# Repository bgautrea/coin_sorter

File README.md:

# Coin Sorter — Computer Vision Pipeline

Real-time coin classifier for an automated sorter. Camera on a Raspberry Pi 5
watches a belt, an ONNX classifier identifies each coin (penny / nickel / dime
/ quarter / reject), and a serial command tells a Raspberry Pi Pico to route
the coin to the correct bin.

```
   CSI camera ──► Pi 5 ──► picamera2 ──► OpenCV ──► ONNX Runtime ──► label, conf
                                                                       │
                                                  USB serial @ 115200 ─┴──► Pico ──► diverter
```

Training happens off-Pi (Google Colab, T4). The Pi never installs torch or
ultralytics — only `onnxruntime` for inference.

## Repo layout

```
coin_sorter/
├── pyproject.toml
├── config.yaml
├── src/coin_sorter/
│   ├── __init__.py    # load_config, configure_logging
│   ├── capture.py     # CLI: capture labelled frames on the Pi
│   ├── dataset.py     # PyTorch Dataset used by the Colab notebook
│   ├── train.py       # reference CLI mirror of the notebook
│   ├── infer.py       # CoinClassifier — ONNX Runtime, with stub fallback
│   ├── pico.py        # serial wrapper for the Pico belt controller
│   └── sorter.py      # main runtime loop
├── notebooks/train_colab.ipynb
├── scripts/zip_dataset.sh, fetch_model.sh
├── data/raw/, data/processed/   (gitignored)
├── models/                       (gitignored)
└── tests/
```

## Pi-side setup (Raspberry Pi OS Bookworm)

### 1. System packages

```bash
sudo apt update
sudo apt install -y \
    python3-picamera2 \
    python3-libcamera \
    python3-pip \
    python3-venv \
    libatlas-base-dev \
    git \
    zip
```

`python3-picamera2` brings in `libcamera` and the Pi-specific camera stack —
those bits are not available from PyPI on the Pi and must come from apt.

### 2. Virtual environment (with system site packages)

Bookworm enforces [PEP 668](https://peps.python.org/pep-0668/) — pip into the
system Python is blocked, and you should not use `--break-system-packages`.
Use a venv. **Critical:** `picamera2` has C extensions tied to the system
`libcamera` build, so the venv has to inherit system site-packages:

```bash
cd ~/coin_sorter
python3 -m venv --system-site-packages .venv
source .venv/bin/activate
pip install --upgrade pip
pip install -e .
```

Verify picamera2 is visible inside the venv:

```bash
python -c "from picamera2 import Picamera2; print('ok')"
```

If you forgot `--system-site-packages`, recreate the venv — installing
picamera2 from PyPI on the Pi is more pain than it is worth.

### 3. Confirm camera + Pico

```bash
libcamera-hello --list-cameras   # should show the Module 3
ls /dev/ttyACM*                  # should show /dev/ttyACM0
groups | tr ' ' '\n' | grep dialout || sudo usermod -aG dialout "$USER"
# log out / back in after adding to dialout
```

## Data capture workflow

Capture is **belt-fed**: a feeder stepper drops coins onto the belt, they pass
under the camera, and a **single-coin gate** decides what gets saved. Each save
is a tight square crop around one whole, isolated coin.

### Labels: (denomination, design, side)

The goal is to pull collectible varieties out of a mixed batch, and the
identifying design is often on **one side only** (a wheat cent's obverse is the
same Lincoln as a memorial cent). So classes are `denomination_design_side`,
e.g. `penny_wheat_rev`, `nickel_buffalo_obv` — see `classifier.labels` in
`config.yaml`, and `sorter.sort_map` for which labels go to the `keep` /
`common` / `check` bins. The `check` bin (coins ambiguous from the visible
side) is simply re-fed: each pass halves it.

The capture flow that follows from this is: **feed one design per batch**, then
**tag sides in the web UI** afterwards (a coin lands heads-up or tails-up at
random).

### Lighting recipe (rig-specific, in `config.local.yaml`)

The internal ring light mirrors off the belt as a specular streak that breaks
detection; the working recipe is the ring **off**, an off-axis **external
light** (switched by hand — check the preview is not black before a run), a
manual short shutter (`exposure_us: 1500`) to freeze belt motion, and manual
white balance. **Do not change WB between batches**: colour is the strongest
cue between denominations, and a WB drift inside one class teaches the model
the tint instead of the coin. Colour robustness comes from augmentation at
training time, applied uniformly to every class.

### Web UI

On the rig it runs as a user systemd service (`deploy/coin-webcal.service`):

```bash
scripts/webcal.sh install                 # once: install + enable at boot (sudo for linger)
scripts/webcal.sh start|stop|restart|status|logs   # shorthand for the commands below
systemctl --user restart coin-webcal      # after config.yaml / label changes
systemctl --user stop coin-webcal         # before CLI capture or flashing the Pico
journalctl --user-unit coin-webcal -f      # logs
python -m coin_sorter.webcal              # or run it by hand; http://<pi-ip>:8080/
```

Live preview with the detection overlay (`area`, `circ`, `fill`, and `sharp` —
a focus figure of merit; peak it on the *face* of a nickel sitting on the belt,
depth of field at this working distance is about ±1 mm), sliders for focus,
WB, exposure, ROI and gate thresholds, and the belt / feeder controls.

**Feeder**: speed plus *burst ms* / *every ms* pulsing. Pulsing is the
coin-spacing knob — the feeder runs in short bursts and the belt clears each
burst before the next. Working values for nickels: 3200 Hz, 300 ms every
1500 ms, belt 550 Hz. The firmware releases both stepper drivers 1 s after
motion stops (an idle TB6600 at full holding current cooked the feeder motor
once); check each driver's current DIPs against its motor's rating — the feeder
is a 0.7 A 17HS4023.

**Capture**: set the label to the *design* you loaded (e.g. `nickel_jefferson`
— the side is added when tagging), Start, then belt → feeder. The count climbs
only for crops that pass the gate.

**Tagging**: in the Captures panel enter the label, Refresh, then **Tag**. Each
crop is shown large; press the number key for its (design, side) class and it
is moved into that folder and the next one appears. `s` skips, `x` deletes,
`Esc` stops. Targets are the configured labels sharing the denomination prefix.

"Show config" emits a `config.local.yaml` snippet with the tuned camera values.
The web UI **owns the camera** — stop it before using the CLI below.

### The single-coin gate

Besides area and circularity, a blob must have `fill` (area ÷ its
min-enclosing-circle area; one coin ≈ 0.95, two overlapping ≈ 0.6) above
`min_fill_frac`, not touch the ROI border, and have no other blob inside its
crop window (`isolate`). Clusters and half-coins are never saved under a class
label. To re-gate crops captured earlier:

```bash
python scripts/prune_crops.py            # report per label
python scripts/prune_crops.py --apply    # move failures to data/raw/_rejected/<label>/
```

`_rejected/` is excluded from training and from `zip_dataset.sh`.

### CLI capture (alternative to the web UI)

```bash
python -m coin_sorter.capture --label _calib --calibrate      # ROI/threshold snapshot
python -m coin_sorter.capture --label nickel_jefferson --count 250 --drive-belt
python -m coin_sorter.capture --label reject --interval 0.4 --count 250   # bypasses the gate
```

`--count` counts coins saved. `dedup_mode` picks one save per coin
(`centroid_band`) or a few pose samples per coin (`min_interval`).

## Training workflow (Colab)

1. **Bundle the dataset on the Pi:**
   ```bash
   ./scripts/zip_dataset.sh
   ```
   Produces `./data.zip`.

2. **Upload to Drive** at `MyDrive/coin_sorter/data.zip`. The notebook reads
   this exact path.

3. **Open `notebooks/train_colab.ipynb` in Colab:**
   - Runtime → Change runtime type → T4 GPU
   - Runtime → Run all
   - The notebook mounts Drive, unzips, trains, prints top-1/top-5, writes a
     confusion matrix, exports ONNX, and copies the result to
     `MyDrive/coin_sorter/models/coin_classifier.onnx`.

4. **Pull the model back to the Pi:**
   ```bash
   # If you have Drive mounted on a workstation:
   ./scripts/fetch_model.sh user@workstation:/path/to/Drive/MyDrive/coin_sorter/models/coin_classifier.onnx

   # Or a local copy:
   ./scripts/fetch_model.sh ~/Downloads/coin_classifier.onnx
   ```
   The model lands at `models/coin_classifier.onnx` (the path in `config.yaml`).

## Deployment

```bash
source .venv/bin/activate
python -m coin_sorter.sorter
```

If `models/coin_classifier.onnx` is missing, the sorter logs a warning and
runs with a stub classifier that always returns `reject` with confidence 0.
This lets you verify the camera and Pico paths before any model exists.

## Configuration

Everything lives in `config.yaml`. Per-machine overrides go in
`config.local.yaml` (gitignored, deep-merged on top). The most useful knobs:

- `camera.width / height` — resolution. 1280×720 is plenty for the classifier
  and keeps frame rate up.
- `model.path` — where the ONNX model is loaded from.
- `model.input_size` — must match the `imgsz` you trained at.
- `classifier.confidence_threshold` — coins below this go to `reject`.
- `classifier.labels` — class order. **Must match alphabetical sort of the
  training class folders** (this is how Ultralytics assigns indices).
- `sorter.cooldown_ms` — guard against double-classifying the same coin.
- `camera.roi` — belt region as `[x, y, w, h]` fractions; capture crops to this.
- `camera.af_mode / lens_position` — Arducam 64MP focus (manual lock recommended
  for the fixed-distance belt; find the value in the web UI or cam_test/stream.py).
- `camera.awb / colour_gains` — white balance; lock it (manual `[red, blue]`) for
  consistent colour under the ring. Tune in the web UI (`coin_sorter.webcal`).
- `capture.*` — the belt-fed capture gate (segmentation method, area/circularity
  thresholds, dedup mode, crop padding). See "Data capture workflow" above and
  the inline comments in `config.yaml`.
- `capture.lights / light_rgb` — WS2812 ring light (Pico GP16); on for every
  session, neutral white by default.

## Troubleshooting

**`ModuleNotFoundError: picamera2`** — Your venv does not see system
site-packages. Recreate with `python -m venv --system-site-packages .venv`.

**`PermissionError: '/dev/ttyACM0'`** — You are not in the `dialout` group.
Run `sudo usermod -aG dialout $USER`, then log out and back in.

**`/dev/ttyACM0` missing** — The Pico is not enumerating. Check the USB cable
(many "charging" cables have no data lines), `dmesg | tail -20` for kernel
hints, or try a different USB port.

**`libcamera-hello` shows no cameras** — Confirm the CSI ribbon is seated
correctly, then ensure `dtoverlay=imx708` (Module 3) or the appropriate
overlay is enabled in `/boot/firmware/config.txt`. Reboot after changes.

**ONNX Runtime warns about provider** — The Pi build of `onnxruntime` from
PyPI ships with CPUExecutionProvider only. `XnnpackExecutionProvider` will
load only if you have an onnxruntime build with XNNPACK enabled; otherwise
CPU is fine — a YOLO-cls nano runs at >30 FPS at 224×224 on the Pi 5.

**Classifier always returns `reject` with confidence 0.0** — The stub is
active. Either the model file is missing, or the path in `config.yaml`
doesn't match where you placed it. Check `ls -lh models/`.

**Wrong class predicted consistently for one class** — Almost always a label-
order mismatch. The order of `classifier.labels` in `config.yaml` must match
`sorted(os.listdir(data_root))` from training time.

## Decisions worth flagging (see the Colab notebook for the full rationale)

- **Base model: YOLO11 nano-cls** by default. v11 trains a bit faster than v8
  for the same accuracy on small classification problems and the API is
  identical (`YOLO('yolo11n-cls.pt')`). Swap to `'yolov8n-cls.pt'` if you want
  to A/B; either is fine.
- **Image size: 224×224.** Coins-as-discs are low-frequency enough that this
  is plenty. If you later need to distinguish e.g. state quarter designs,
  bump to 320 or 384 (and update both `training.imgsz` and `model.input_size`).
- **Class imbalance.** Easiest fix is collecting balanced data — aim for the
  same image count per class. If that's impractical, oversample the minority
  classes (Ultralytics doesn't expose loss weighting cleanly for cls). The
  notebook prints a confusion matrix — watch for one row consistently mis-
  classified, that's the signal.
- **Augmentation.** Full 360° rotation is non-optional (coins land in any
  orientation). HSV jitter handles copper-vs-silver lighting drift. Avoid
  random crop / perspective — those distort the coin's circular outline,
  which is genuine signal.
- **ONNX export.** `dynamic=False` + fixed `imgsz` gives the smallest, fastest
  graph. Opset 17 is well-supported by onnxruntime 1.17+. If you ever change
  `imgsz`, re-export — input shape is baked in.

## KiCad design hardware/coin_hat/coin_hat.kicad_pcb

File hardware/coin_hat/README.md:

# Coin sorter HAT+ — rev 1

KiCad project for a Pi 5 HAT+ that carries the whole motion side of the
sorter: 12 V in, buck to 5 V for the Pi, a Raspberry Pi Pico, two StepStick
sockets (TMC2209 or A4988, selected by solder jumpers) for belt and feeder, the
MG996R diverter servo on its own buck, switched 12 V outputs, and the small
stuff (LED ring level shifter, feeder home switch, coin sensor, HAT+ ID EEPROM).

The board runs **lengthwise** along the Pi: 122 × 56.5 mm, the same width as the
Pi. The HAT+ holes and header sit at one end, and a 57 mm overhang runs past the
Pi's SD-card / PCIe end, so the drivers, jack and bucks sit over nothing. The
Pi + HAT stack is 142 × 56.5 mm, a slim box instead of rev 0's 85 × 90. The
overhang goes off the SD end, not the USB end: at 16 mm spacer height, a board
over the USB/Ethernet jacks would sit on top of the plugs.

Generated by a script, so it is a *netlist with symbols placed on a sheet*, not
a drawn schematic: every pin carries a global label and the parts are grouped by
function. Redraw with wires or leave it — KiCad is happy either way.

## Rev 1 changes (2026-09-27)

- **Diverter is the MG996R servo, not a stepper.** U4 socket, its jumpers
  JP41–44, the 4-pin motor connector and C5 are gone, and so is the diverter
  home switch (J8), because the servo is absolute. New parts: U8 is a separate
  12 V → 5–6 V buck just for the servo (+SERVO). J4 is a 3-pin 0.1" servo
  header (1 SIG, 2 V+, 3 GND). C6 is 1000 µF placed *at* J4. D5 lights when the
  servo rail is live, and GP27 reads the servo rail through a 10k/10k divider.
  GP6 drives the signal pin directly, with no series resistor and no pulldown.
  That is how the bench build works.
- **Why the LED and the sense line:** if the servo rail is dead and GP6 is
  pulsing, the servo back-powers through its signal pin. It twitches and never
  moves, which looks exactly like a signal fault. Check D5 (or GP27) first.
- **Outline goes lengthwise** (see above), with the **CSI/DSI FPC notch**
  (10 × 16.5 mm on the bottom edge, per the HAT+ spec's M.2 HAT+ drawing). Rev 0
  had no notch and would have blocked the camera cable.
- **Header position fixed.** Rev 0 had it 1.27 mm off in both axes. HAT+ spec:
  the header centre is 29 mm from the left hole, on the hole line, so pin 1 is
  at (8.37, 4.77) from the Pi corner and pin 2 is at (8.37, 2.23).
- **Diode polarity fixed.** KiCad diode and LED footprints put the cathode on
  pad 1, and rev 0's symbols had the anode on pin 1. D3/D4 flybacks would have
  shorted 12 V to ground when the key light or aux output switched on, D1
  would have blocked the Pico's VSYS, and D5 would never light.
- **StepStick pin numbering fixed.** Rev 0's symbol numbered pins 1 = EN …
  16 = GND. The `Pololu_Breakout-16` footprint is 1 = GND, 2 = VDD, 3–6 = motor,
  7 = GND, 8 = VMOT, 9 = EN … 16 = DIR, so every driver pin would have landed
  on the wrong pad.
- **Verified with KiCad 9:** ERC shows 0 errors (the remaining warnings are
  off-grid pins and the embedded `coin_hat` symbol library). Every symbol pin
  number exists as a pad on its footprint, and there are no single-node nets.
  DRC on the outline shows 0 violations. The floor plan on `User.Comments` is
  the real courtyards (buck modules as their 17.8 × 20.3 boards), checked for
  overlaps, holes, header and notch. 57 mm is the shortest overhang that packs
  cleanly; 52 mm clashes.

## Files

- `coin_hat.kicad_pro` / `coin_hat.kicad_sch` — open this. Symbols are embedded;
  footprints point at the stock KiCad 8 libraries. **Tools → Update PCB from
  Schematic** pulls all footprints into the board.
- `coin_hat.pretty/` + `fp-lib-table` — project footprint library with the
  two Pololu buck modules. Pad and mounting-hole positions come from Pololu's
  drill-guide DXFs (`reg15d01-drill.dxf` for the D24V50F5, `reg24g-drill.dxf`
  for the D36V28Fx), drawn top view with pad 1 = EN (square):
  - D24V50F5: one row EN, VIN, GND, GND, VOUT along a 0.7" edge.
  - D36V28Fx: the same row, plus PG 0.1" inboard of EN.
  - Both: #2 (2.2 mm) mounting holes in opposite corners.
  EN is left open on both (each module has a 100 kΩ pull-up to VIN), and PG
  is unused.
- `coin_hat.kicad_pcb` — placed and fully routed 2-layer board, 122 × 56.5 mm
  (see Routing).
- `make_fab.py` — regenerates everything in `fab/` from the schematic and board
  (`python3 hardware/coin_hat/make_fab.py`).
- `fab/` — ready to upload (see Ordering).

## Pin map (Pico)

| Function | Pins | Notes |
|---|---|---|
| Pi link | GP0 TX / GP1 RX (UART0) | Pi GPIO14/15, `/dev/ttyAMA0`, `dtparam=uart0=on`. REPL stays on USB. |
| Belt | STEP GP2, DIR GP3, EN GP4 | unchanged from `firmware/main.py`; TMC UART addr 0 |
| Diverter servo | GP6 → J4 signal | unchanged from `firmware/main.py`; direct, no resistors |
| Servo rail sense | GP27 (ADC1) | 10k / 10k: 5.4 V → 2.7 V, 6 V → 3.0 V |
| Feeder | STEP GP18, DIR GP19, EN GP22 | TMC UART addr 1 |
| TMC UART | GP20 TX via 1 k, GP21 RX | single-wire bus shared by both drivers |
| Feeder home | GP11 | to GND, internal pull-up |
| Coin sensor | GP5 | 3-pin XH |
| Key light / aux MOSFET | GP14 / GP15 | AO3400, flyback diode, 2-pin terminals |
| LED ring | GP16 → 74AHCT1G125 → 5 V data | 3-pin XH |
| VMOT sense | GP28 | 100 k / 15 k: 12 V → 1.57 V |
| Aux header | GP7, GP9, GP17, GP12/13 (I²C), GP26 (ADC0) | plus 3V3/GND |
| Spare | GP8, GP10 | no-connect |

The Pi resets the Pico by driving **GPIO17 high**, which makes Q3 pull RUN low.
It is active-high on purpose: GPIO17 defaults to pull-down at boot, so an
unconfigured Pi leaves the Pico running. `pinctrl set 17 op dh; sleep 0.1;
pinctrl set 17 dl` replaces the USB DTR toggle that relaunches `main.py` today.

## Power

Jack → F1 (mini blade) → +12 V bus. The bus feeds:

- the StepSticks (100 µF each) and the switched outputs;
- U5 (12 → 5 V, 5 A module) → +5 V → Pi header pins 2/4, and Pico VSYS
  through D1;
- U8 (12 → 5–6 V, ~3 A module) → +SERVO → J4.

U5 is a Pololu D24V50F5. For U8, any D36V28Fx fits the same footprint: the F5 (5 V) or the F6 (6 V). The MG996R
is rated 4.8–7.2 V, and 6 V gives more torque than the 5.4 V bench supply.

Feeding a Pi 5 over the header skips USB-PD, so set `usb_max_current_enable=1`
if USB peripherals need more than 600 mA. Size F1 to the real load: Pi 5 up to
~2.3 A at 12 V, plus two steppers, plus the servo (1.4 A stall at 6 V ≈ 0.8 A
at 12 V).

## Mechanical

- 16 mm board-to-board spacers (HAT+ spec recommendation for the Active
  Cooler) and a matching stacking header. Keep the bottom side clear over
  the Pi (Pico zone) and over the Pi 5 PoE header, which is marked on the
  board.
- The Pi 5 PCIe FFC connector sits under the overhang near the Pi edge. It is
  unused here, and a flat cable would still pass under a 16 mm-high board.
- The motor connectors, fuse and jack are on the left end so a case can have
  one connector wall. J5 is a CUI PJ-102AH (5 A, 5.5 × 2.1 plug).
- Copper keepouts around the four HAT+ holes: 3.1 mm radius on the bottom,
  where the metal standoff sits (and is likely tied to the Pi's ground), and
  2.6 mm on top, under the screw head.

## Routing

Two layers, 1 oz, every net routed. KiCad 9 DRC: 0 violations, 0 unconnected,
0 schematic-parity issues.

| Net class | Nets | Track |
|---|---|---|
| HighCurrent | VIN_RAW, +12V, +5V | 1.5 mm |
| Power | +SERVO, VSYS_PICO, switched 12 V outputs | 1.0 mm |
| Motor | stepper coil nets | 0.6 mm |
| Ground | GND (the pours carry the current) | 0.35 mm |
| Default | signals | 0.25 mm / 0.2 mm space |

Signal vias are 0.6/0.3 mm. Power-net vias are 1.2/0.6 mm (about 3 A each),
except one 0.8/0.4 mm AUX_SW via in a tight spot, so rate J12 (aux 12 V out) at
about 1.5 A. GND is poured on both layers. Five GND pads connect solid to the
pour rather than through thermal spokes: U3.7, J10.2, J1.14, C6.2 and one Pico
GND pad. Give those a hotter iron.

Freerouting did the autorouting, except for the Pi 5 V feed, which is
hand-placed and locked. J1 pins 2/4 are boxed in by the mounting hole, the board
edge and the other header pins, so the feed runs 1.5 mm on F.Cu from U5 VOUT,
passes under the hole, and necks to 1.0 mm for the last ~3 mm beside pin 1.
Official HAT+ boards squeeze through the same gap.

The Pico sits with its USB socket at the board's right edge, so a micro-USB
cable plugs in for REPL and `mpremote`. The HAT+ ID EEPROM group (U7,
R10–R12, JP1, C8) sits in the pocket left of the Pico. U6 and U7 each have a
100 nF bypass cap (C7, C8).

Silkscreen: labels for JLCPCB-placed parts are on F.Fab only (the placement
file carries them). JP21/22/23 and JP32/33 had no room for a readable label, so
read the jumper columns top to bottom: JP21→JP24 beside U2 (belt) and JP31→JP34
beside U3 (feeder). JP24, JP31 and JP34 are labelled, and the 2-pad MS1/MS2
jumpers sit above the 3-pad ones.

## Ordering

Everything is in `fab/`:

- `coin_hat_gerbers.zip` — Gerbers + Excellon drill (separate PTH/NPTH). Both
  fabs take it. Specs: 2 layers, 122 × 56.5 mm, 1.6 mm FR-4, 1 oz, smallest
  drill 0.3 mm, track/space 0.25/0.2 mm. Standard capabilities at both.
- **JLCPCB** — `jlcpcb/coin_hat_bom_jlcpcb.csv` + `jlcpcb/coin_hat_cpl_jlcpcb.csv`.
  Assembly: top side only, 25 placements, 12 unique parts. All resistors,
  the AO3400A and the SS34 are Basic parts. The SMBJ15A is "preferred
  extended" (no setup fee). The level shifter, EEPROM and LED are Extended
  (JLC's per-part loading fee).
- **PCBWay** — `pcbway/coin_hat_bom_pcbway.csv` (every part, with through-hole
  lines marked "customer solders") + `pcbway/coin_hat_centroid_pcbway.csv`.

Check before you pay:

- **JLCPCB's placement preview.** KiCad and JLC orient some packages
  differently. The CPL applies the usual corrections (SOT-23 / SC-70 +180°,
  SOIC +270°), but check every part, and especially the cathode bars on
  D1–D4 and the LED.
- U1 (Pico) and the solder jumpers are deliberately left out of assembly. The
  Pico's pads have no paste, so the stencil leaves them bare. You solder the
  Pico by its castellations. KiCad DRC reports U1 as "differs from library"
  for that reason. That warning is expected.
- Hand-soldered: J1 is a 2×20, 2.54 mm female socket on the **bottom** side.
  It is not in the BOMs, and its height matters. With 16 mm spacers, the Pi's
  pins (8.5 mm tall) only engage a socket body of H mm by H − 7.5 mm, so a
  standard 8.5 mm socket barely touches. Use an 11–13 mm tall socket. The
  StepStick sockets are 2× 1×8 female headers per driver.
- Trim through-hole leads flush over the Pi (J6/J7/J9–J12). The Active Cooler
  sits under that area, and the HAT+ spec asks for extra clearance if the
  underside isn't flat.
- Power only through the 12 V jack while the HAT is fitted. U5 feeds the Pi's
  5 V rail directly, with nothing to stop backfeed if the Pi's USB-C is also
  plugged in. U5 also regulates to 5.0 V, not the 5.1 V the Pi's own supply
  gives. That's fine, but it leaves less headroom before the under-voltage
  warning if a heavy USB load is attached.

## Verify before ordering

- TMC2209 breakout pin order (the 16-pin socket varies between makers; DIAG /
  INDEX are often extra pins outside it).
- Solder jumpers per driver socket (JPx1–JPx4) match the driver you fit:
  **TMC2209** — JPx3=A (UART on pin 4), JPx4=A (CLK→GND), JPx1/JPx2 = UART
  address (belt 00, feeder 10). **A4988** — JPx3=B (MS3 high), JPx4=B (RESET
  tied to SLEEP), JPx1+JPx2 closed = 1/16 step; set Vref = I × 8 × Rsense
  (0.40 V for 0.5 A with R100 sense resistors); heatsink.
- Buck modules sit on 0.1" header pins in the `coin_hat:Pololu_*` footprints.
  Order the modules with their header strip, or use a low-profile socket.
- J4 pin order vs your servo plug (usual order: signal, V+, GND; brown wire =
  GND).
- Header, holes and FPC notch against the official Pi 5 mechanical drawing. The
  socket goes on the **bottom** side.
- Belt motor current rating (TMC2209 tops out around 2 A RMS).

## Firmware implications

The feeder moves to DIR/EN on GP19/GP22, and the Pi link moves from USB CDC to
UART0. Current and hold settings move from DIP switches to TMC UART writes. The
servo stays on GP6 exactly as `firmware/main.py` drives it today; optionally
read GP27 and refuse to pulse GP6 while the servo rail is down. None of this
changes the serial protocol the Pi speaks.

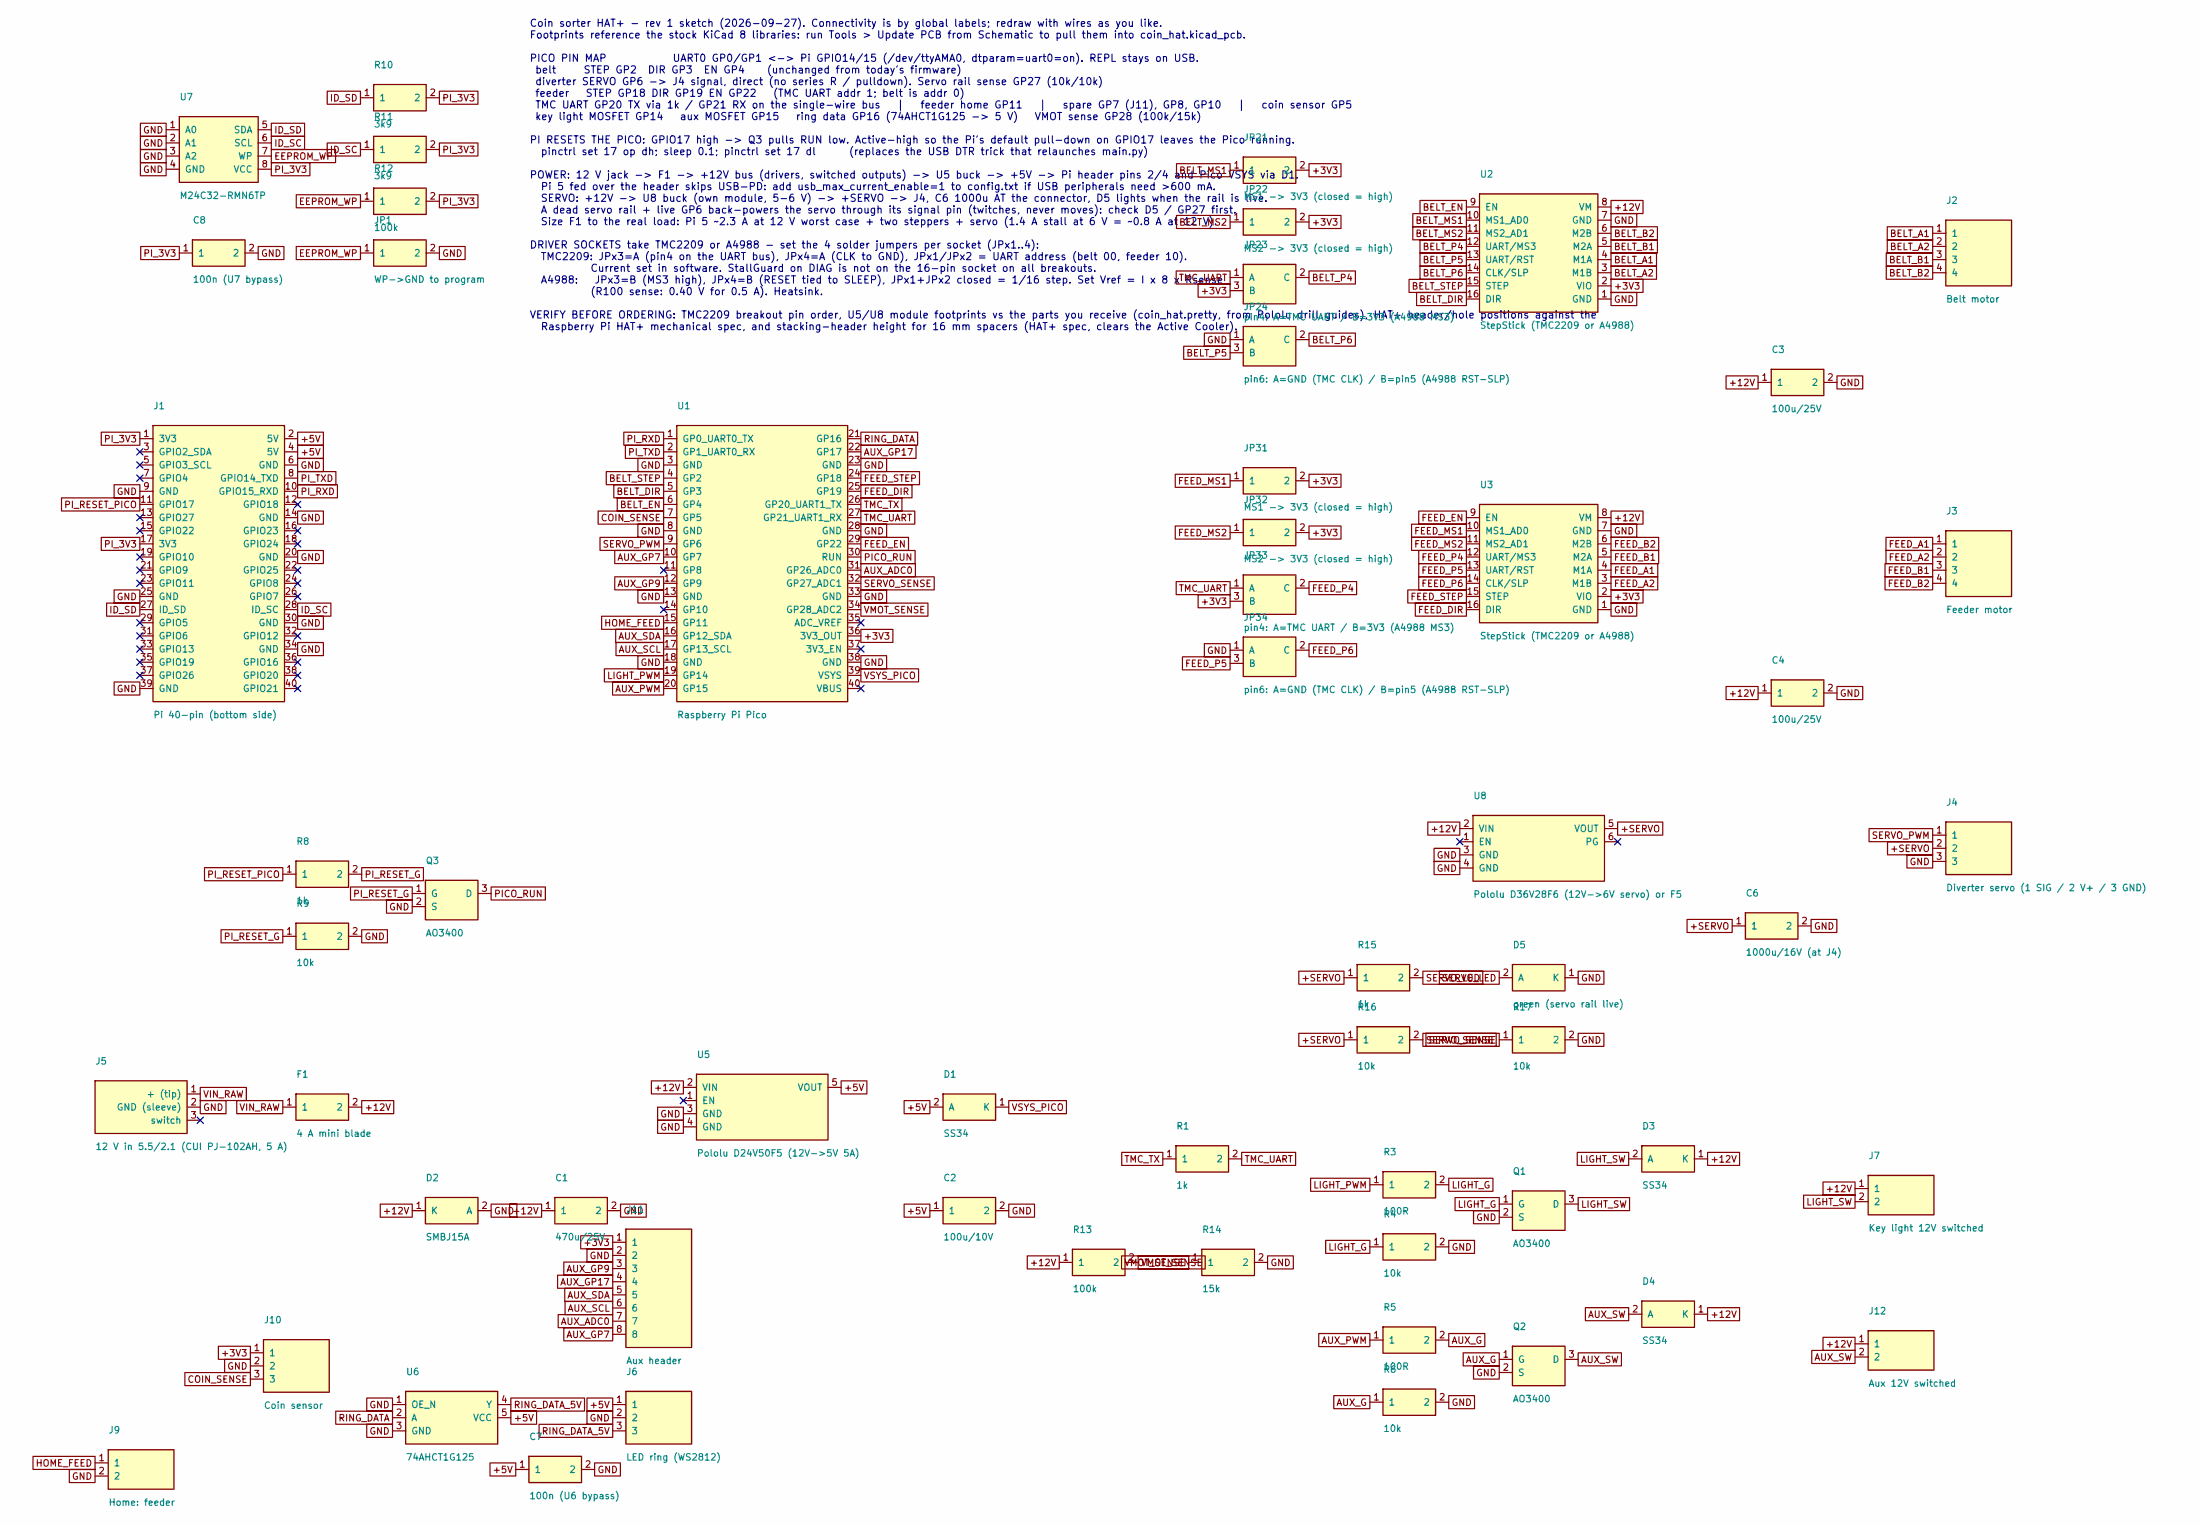
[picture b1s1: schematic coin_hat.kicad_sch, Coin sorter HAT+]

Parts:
C1: 470u/25V; CP_Radial_D10.0mm_P5.00mm
C2: 100u/10V; CP_Radial_D8.0mm_P3.50mm
C3, C4: 100u/25V; CP_Radial_D8.0mm_P3.50mm
C6: 1000u/16V (at J4); CP_Radial_D10.0mm_P5.00mm
C7: 100n (U6 bypass); C_0603_1608Metric; MPN CC0603KRX7R9BB104; LCSC C14663
C8: 100n (U7 bypass); C_0603_1608Metric; MPN CC0603KRX7R9BB104; LCSC C14663
D1, D3, D4: SS34; D_SMA; MPN SS34; LCSC C8678
D2: SMBJ15A; D_SMB; MPN SMBJ15A; LCSC C19077569
D5: green (servo rail live); LED_0603_1608Metric; MPN XL-1608UGC-04; LCSC C965804
F1: 4 A mini blade; Fuseholder_Blade_Mini_Keystone_3568; MPN 3568 holder + 4 A mini blade fuse
J1: Pi 40-pin (bottom side); PinSocket_2x20_P2.54mm_Vertical
J2: Belt motor; JST_XH_B4B-XH-A_1x04_P2.50mm_Vertical; MPN B4B-XH-A(LF)(SN); LCSC C144395
J3: Feeder motor; JST_XH_B4B-XH-A_1x04_P2.50mm_Vertical; MPN B4B-XH-A(LF)(SN); LCSC C144395
J4: Diverter servo (1 SIG / 2 V+ / 3 GND); PinHeader_1x03_P2.54mm_Vertical
J5: 12 V in 5.5/2.1 (CUI PJ-102AH, 5 A); BarrelJack_CUI_PJ-102AH_Horizontal; MPN PJ-102AH; LCSC C3096093
J6: LED ring (WS2812); JST_XH_B3B-XH-A_1x03_P2.50mm_Vertical; MPN B3B-XH-A(LF)(SN); LCSC C144394
J7: Key light 12V switched; JST_XH_B2B-XH-A_1x02_P2.50mm_Vertical; MPN B2B-XH-A(LF)(SN); LCSC C158012
J9: Home: feeder; JST_XH_B2B-XH-A_1x02_P2.50mm_Vertical; MPN B2B-XH-A(LF)(SN); LCSC C158012
J10: Coin sensor; JST_XH_B3B-XH-A_1x03_P2.50mm_Vertical; MPN B3B-XH-A(LF)(SN); LCSC C144394
J11: Aux header; PinHeader_1x08_P2.54mm_Vertical
J12: Aux 12V switched; JST_XH_B2B-XH-A_1x02_P2.50mm_Vertical; MPN B2B-XH-A(LF)(SN); LCSC C158012
JP1: WP->GND to program; SolderJumper-2_P1.3mm_Open_RoundedPad1.0x1.5mm
JP21, JP31: MS1 -> 3V3 (closed = high); SolderJumper-2_P1.3mm_Open_RoundedPad1.0x1.5mm
JP22, JP32: MS2 -> 3V3 (closed = high); SolderJumper-2_P1.3mm_Open_RoundedPad1.0x1.5mm
JP23, JP33: pin4: A=TMC UART / B=3V3 (A4988 MS3); SolderJumper-3_P1.3mm_Open_RoundedPad1.0x1.5mm
JP24, JP34: pin6: A=GND (TMC CLK) / B=pin5 (A4988 RST-SLP); SolderJumper-3_P1.3mm_Open_RoundedPad1.0x1.5mm
Q1, Q2, Q3: AO3400; SOT-23; MPN AO3400A; LCSC C20917
R1, R8, R15: 1k; R_0603_1608Metric; MPN 0603WAF1001T5E; LCSC C21190
R3, R5: 100R; R_0603_1608Metric; MPN 0603WAF1000T5E; LCSC C22775
R4, R6, R9, R16, R17: 10k; R_0603_1608Metric; MPN 0603WAF1002T5E; LCSC C25804
R10, R11: 3k9; R_0603_1608Metric; MPN 0603WAF3901T5E; LCSC C23018
R12, R13: 100k; R_0603_1608Metric; MPN 0603WAF1003T5E; LCSC C25803
R14: 15k; R_0603_1608Metric; MPN 0603WAF1502T5E; LCSC C22809
U1: Raspberry Pi Pico; RaspberryPi_Pico_SMD_HandSolder; MPN Raspberry Pi Pico (SC0915)
U2, U3: StepStick (TMC2209 or A4988); Pololu_Breakout-16_15.2x20.3mm
U5: Pololu D24V50F5 (12V->5V 5A); Pololu_D24V50F5; MPN D24V50F5 (#2851)
U6: 74AHCT1G125; SOT-353_SC-70-5; MPN SN74AHCT1G125DCKR; LCSC C350557
U7: M24C32-RMN6TP; SOIC-8_3.9x4.9mm_P1.27mm; MPN M24C32-RMN6TP; LCSC C79920
U8: Pololu D36V28F6 (12V->6V servo) or F5; Pololu_D36V28Fx; MPN D36V28F6 (#3783)

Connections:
+3V3: J10.1, J11.1, JP21.2, JP22.2, JP23.3 (B), JP31.2, JP32.2, JP33.3 (B), U1.36 (3V3_OUT), U2.2 (VIO), U3.2 (VIO)
+5V: C2.1, C7.1, D1.2 (A), J1.2 (5V), J1.4 (5V), J6.1, U5.5 (VOUT), U6.5 (VCC)
+12V: C1.1, C3.1, C4.1, D2.1 (K), D3.1 (K), D4.1 (K), F1.2, J7.1, J12.1, R13.1, U2.8 (VM), U3.8 (VM), U5.2 (VIN), U8.2 (VIN)
+SERVO: C6.1, J4.2, R15.1, R16.1, U8.5 (VOUT)
AUX_ADC0: J11.7, U1.31 (GP26_ADC0)
AUX_G: Q2.1 (G), R5.2, R6.1
AUX_GP7: J11.8, U1.10 (GP7)
AUX_GP9: J11.3, U1.12 (GP9)
AUX_GP17: J11.4, U1.22 (GP17)
AUX_PWM: R5.1, U1.20 (GP15)
AUX_SCL: J11.6, U1.17 (GP13_SCL)
AUX_SDA: J11.5, U1.16 (GP12_SDA)
AUX_SW: D4.2 (A), J12.2, Q2.3 (D)
BELT_A1: J2.1, U2.4 (M1A)
BELT_A2: J2.2, U2.3 (M1B)
BELT_B1: J2.3, U2.5 (M2A)
BELT_B2: J2.4, U2.6 (M2B)
BELT_DIR: U1.5 (GP3), U2.16 (DIR)
BELT_EN: U1.6 (GP4), U2.9 (EN)
BELT_MS1: JP21.1, U2.10 (MS1_AD0)
BELT_MS2: JP22.1, U2.11 (MS2_AD1)
BELT_P4: JP23.2 (C), U2.12 (UART/MS3)
BELT_P5: JP24.3 (B), U2.13 (UART/RST)
BELT_P6: JP24.2 (C), U2.14 (CLK/SLP)
BELT_STEP: U1.4 (GP2), U2.15 (STEP)
COIN_SENSE: J10.3, U1.7 (GP5)
EEPROM_WP: JP1.1, R12.1, U7.7 (WP)
FEED_A1: J3.1, U3.4 (M1A)
FEED_A2: J3.2, U3.3 (M1B)
FEED_B1: J3.3, U3.5 (M2A)
FEED_B2: J3.4, U3.6 (M2B)
FEED_DIR: U1.25 (GP19), U3.16 (DIR)
FEED_EN: U1.29 (GP22), U3.9 (EN)
FEED_MS1: JP31.1, U3.10 (MS1_AD0)
FEED_MS2: JP32.1, U3.11 (MS2_AD1)
FEED_P4: JP33.2 (C), U3.12 (UART/MS3)
FEED_P5: JP34.3 (B), U3.13 (UART/RST)
FEED_P6: JP34.2 (C), U3.14 (CLK/SLP)
FEED_STEP: U1.24 (GP18), U3.15 (STEP)
GND: C1.2, C2.2, C3.2, C4.2, C6.2, C7.2, C8.2, D2.2 (A), D5.1 (K), J1.6 (GND), J1.9 (GND), J1.14 (GND), J1.20 (GND), J1.25 (GND), J1.30 (GND), J1.34 (GND), J1.39 (GND), J4.3, J5.2 (GND (sleeve)), J6.2, J9.2, J10.2, J11.2, JP1.2, JP24.1 (A), JP34.1 (A), Q1.2 (S), Q2.2 (S), Q3.2 (S), R4.2, R6.2, R9.2, R14.2, R17.2, U1.3 (GND), U1.8 (GND), U1.13 (GND), U1.18 (GND), U1.23 (GND), U1.28 (GND), U1.33 (GND), U1.38 (GND), U2.1 (GND), U2.7 (GND), U3.1 (GND), U3.7 (GND), U5.3 (GND), U5.4 (GND), U6.1 (OE_N), U6.3 (GND), U7.1 (A0), U7.2 (A1), U7.3 (A2), U7.4 (GND), U8.3 (GND), U8.4 (GND)
HOME_FEED: J9.1, U1.15 (GP11)
ID_SC: J1.28 (ID_SC), R11.1, U7.6 (SCL)
ID_SD: J1.27 (ID_SD), R10.1, U7.5 (SDA)
LIGHT_G: Q1.1 (G), R3.2, R4.1
LIGHT_PWM: R3.1, U1.19 (GP14)
LIGHT_SW: D3.2 (A), J7.2, Q1.3 (D)
PICO_RUN: Q3.3 (D), U1.30 (RUN)
PI_3V3: C8.1, J1.1 (3V3), J1.17 (3V3), R10.2, R11.2, R12.2, U7.8 (VCC)
PI_RESET_G: Q3.1 (G), R8.2, R9.1
PI_RESET_PICO: J1.11 (GPIO17), R8.1
PI_RXD: J1.10 (GPIO15_RXD), U1.1 (GP0_UART0_TX)
PI_TXD: J1.8 (GPIO14_TXD), U1.2 (GP1_UART0_RX)
RING_DATA: U1.21 (GP16), U6.2 (A)
RING_DATA_5V: J6.3, U6.4 (Y)
SERVO_LED: D5.2 (A), R15.2
SERVO_PWM: J4.1, U1.9 (GP6)
SERVO_SENSE: R16.2, R17.1, U1.32 (GP27_ADC1)
TMC_TX: R1.1, U1.26 (GP20_UART1_TX)
TMC_UART: JP23.1 (A), JP33.1 (A), R1.2, U1.27 (GP21_UART1_RX)
VIN_RAW: F1.1, J5.1 (+ (tip))
VMOT_SENSE: R13.2, R14.1, U1.34 (GP28_ADC2)
VSYS_PICO: D1.1 (K), U1.39 (VSYS)

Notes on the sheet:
Coin sorter HAT+ - rev 1 sketch (2026-09-27). Connectivity is by global labels; redraw with wires as you like. Footprints reference the stock KiCad 8 libraries: run Tools > Update PCB from Schematic to pull them into coin_hat.kicad_pcb. PICO PIN MAP UART0 GP0/GP1 <-> Pi GPIO14/15 (/dev/ttyAMA0, dtp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

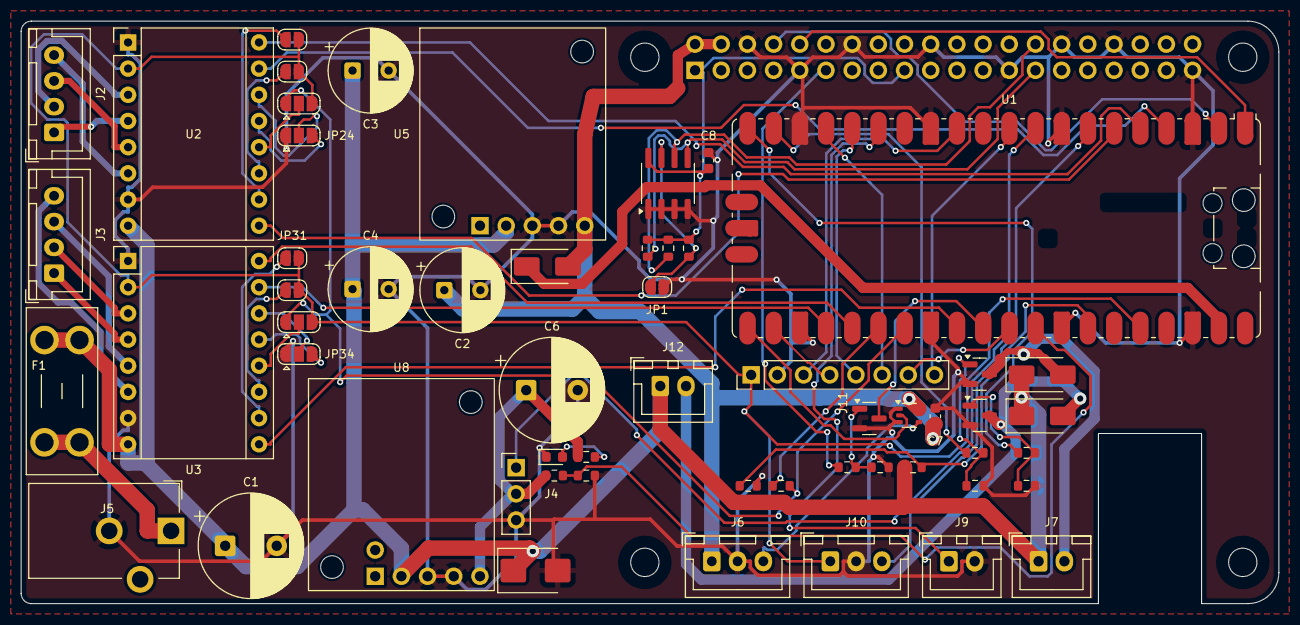
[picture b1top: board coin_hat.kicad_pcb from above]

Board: 2 copper layers, 122.0 x 56.5 mm, 58 parts (1 on the bottom side), 62 nets.

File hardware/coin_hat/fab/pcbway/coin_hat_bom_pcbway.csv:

Item #,Designator,Qty,Manufacturer,Mfg Part #,Description / Value,Package/Footprint,Type,Your Instructions / Notes
1,C1,1,,,470u/25V,CP_Radial_D10.0mm_P5.00mm,THT/module,Do not assemble - customer solders
2,C2,1,,,100u/10V,CP_Radial_D8.0mm_P3.50mm,THT/module,Do not assemble - customer solders
3,"C3,C4",2,,,100u/25V,CP_Radial_D8.0mm_P3.50mm,THT/module,Do not assemble - customer solders
4,C6,1,,,1000u/16V (at J4),CP_Radial_D10.0mm_P5.00mm,THT/module,Do not assemble - customer solders
5,C7,1,YAGEO,CC0603KRX7R9BB104,100n (U6 bypass),C_0603_1608Metric,SMD,Assemble (LCSC C14663)
6,C8,1,YAGEO,CC0603KRX7R9BB104,100n (U7 bypass),C_0603_1608Metric,SMD,Assemble (LCSC C14663)
7,"D1,D3,D4",3,MDD,SS34,SS34,D_SMA,SMD,Assemble (LCSC C8678)
8,D2,1,,SMBJ15A,SMBJ15A,D_SMB,SMD,Assemble (LCSC C19077569)
9,D5,1,XINGLIGHT,XL-1608UGC-04,green (servo rail live),LED_0603_1608Metric,SMD,Assemble (LCSC C965804)
10,F1,1,Keystone,3568 holder + 4 A mini blade fuse,4 A mini blade,Fuseholder_Blade_Mini_Keystone_3568,THT/module,Do not assemble - customer solders
11,J1,1,,,Pi 40-pin (bottom side),PinSocket_2x20_P2.54mm_Vertical,THT/module,Do not assemble - customer solders
12,J2,1,JST,B4B-XH-A(LF)(SN),Belt motor,JST_XH_B4B-XH-A_1x04_P2.50mm_Vertical,THT/module,Do not assemble - customer solders (LCSC C144395)
13,J3,1,JST,B4B-XH-A(LF)(SN),Feeder motor,JST_XH_B4B-XH-A_1x04_P2.50mm_Vertical,THT/module,Do not assemble - customer solders (LCSC C144395)
14,J4,1,,,Diverter servo (1 SIG / 2 V+ / 3 GND),PinHeader_1x03_P2.54mm_Vertical,THT/module,Do not assemble - customer solders
15,J5,1,CUI Devices,PJ-102AH,"12 V in 5.5/2.1 (CUI PJ-102AH, 5 A)",BarrelJack_CUI_PJ-102AH_Horizontal,THT/module,Do not assemble - customer solders (LCSC C3096093)
16,J6,1,JST,B3B-XH-A(LF)(SN),LED ring (WS2812),JST_XH_B3B-XH-A_1x03_P2.50mm_Vertical,THT/module,Do not assemble - customer solders (LCSC C144394)
17,J7,1,JST,B2B-XH-A(LF)(SN),Key light 12V switched,JST_XH_B2B-XH-A_1x02_P2.50mm_Vertical,THT/module,Do not assemble - customer solders (LCSC C158012)
18,J9,1,JST,B2B-XH-A(LF)(SN),Home: feeder,JST_XH_B2B-XH-A_1x02_P2.50mm_Vertical,THT/module,Do not assemble - customer solders (LCSC C158012)
19,J10,1,JST,B3B-XH-A(LF)(SN),Coin sensor,JST_XH_B3B-XH-A_1x03_P2.50mm_Vertical,THT/module,Do not assemble - customer solders (LCSC C144394)
20,J11,1,,,Aux header,PinHeader_1x08_P2.54mm_Vertical,THT/module,Do not assemble - customer solders
21,J12,1,JST,B2B-XH-A(LF)(SN),Aux 12V switched,JST_XH_B2B-XH-A_1x02_P2.50mm_Vertical,THT/module,Do not assemble - customer solders (LCSC C158012)
22,"Q1,Q2,Q3",3,Alpha & Omega,AO3400A,AO3400,SOT-23,SMD,Assemble (LCSC C20917)
23,"R1,R8,R15",3,UNI-ROYAL,0603WAF1001T5E,1k,R_0603_1608Metric,SMD,Assemble (LCSC C21190)
24,"R3,R5",2,UNI-ROYAL,0603WAF1000T5E,100R,R_0603_1608Metric,SMD,Assemble (LCSC C22775)
25,"R4,R6,R9,R16,R17",5,UNI-ROYAL,0603WAF1002T5E,10k,R_0603_1608Metric,SMD,Assemble (LCSC C25804)
26,"R10,R11",2,UNI-ROYAL,0603WAF3901T5E,3k9,R_0603_1608Metric,SMD,Assemble (LCSC C23018)
27,"R12,R13",2,UNI-ROYAL,0603WAF1003T5E,100k,R_0603_1608Metric,SMD,Assemble (LCSC C25803)
28,R14,1,UNI-ROYAL,0603WAF1502T5E,15k,R_0603_1608Metric,SMD,Assemble (LCSC C22809)
29,U1,1,Raspberry Pi,Raspberry Pi Pico (SC0915),Raspberry Pi Pico,RaspberryPi_Pico_SMD_HandSolder,THT/module,Do not assemble - customer solders
30,"U2,U3",2,,,StepStick (TMC2209 or A4988),Pololu_Breakout-16_15.2x20.3mm,THT/module,Do not assemble - customer solders
31,U5,1,Pololu,D24V50F5 (#2851),Pololu D24V50F5 (12V->5V 5A),Pololu_D24V50F5,THT/module,Do not assemble - customer solders
32,U6,1,Texas Instruments,SN74AHCT1G125DCKR,74AHCT1G125,SOT-353_SC-70-5,SMD,Assemble (LCSC C350557)
33,U7,1,STMicroelectronics,M24C32-RMN6TP,M24C32-RMN6TP,SOIC-8_3.9x4.9mm_P1.27mm,SMD,Assemble (LCSC C79920)
34,U8,1,Pololu,D36V28F6 (#3783),Pololu D36V28F6 (12V->6V servo) or F5,Pololu_D36V28Fx,THT/module,Do not assemble - customer solders
